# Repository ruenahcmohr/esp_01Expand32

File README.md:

# esp_01Expand32
esp-01 (esp8266) IO expander, 16 output, 16 input = 32

internet inspired esp-01 (esp8266) IO expander.

This uses DIP (socket and replace if you oops) 74xx595 and 74xx165 chips to give you 16 inputs and 16 outputs from an esp-01

Why not just use i2c?

 WELL, the i2c chips have realy primitive IO circuits, and you cannot have a high impedence input. This means you can't tie into analog circuits like RC pairs to give you time delays, which is something important to me.

 You also can't properly drive an output high, this is also important to me.

The zip file is all the gerber files to have it made.

The regultor is an AMS1117-3.3

oh yea, the power and IO are 5V., IF YOU WANT, you can bypass the regulator and use it all with 3.3V.

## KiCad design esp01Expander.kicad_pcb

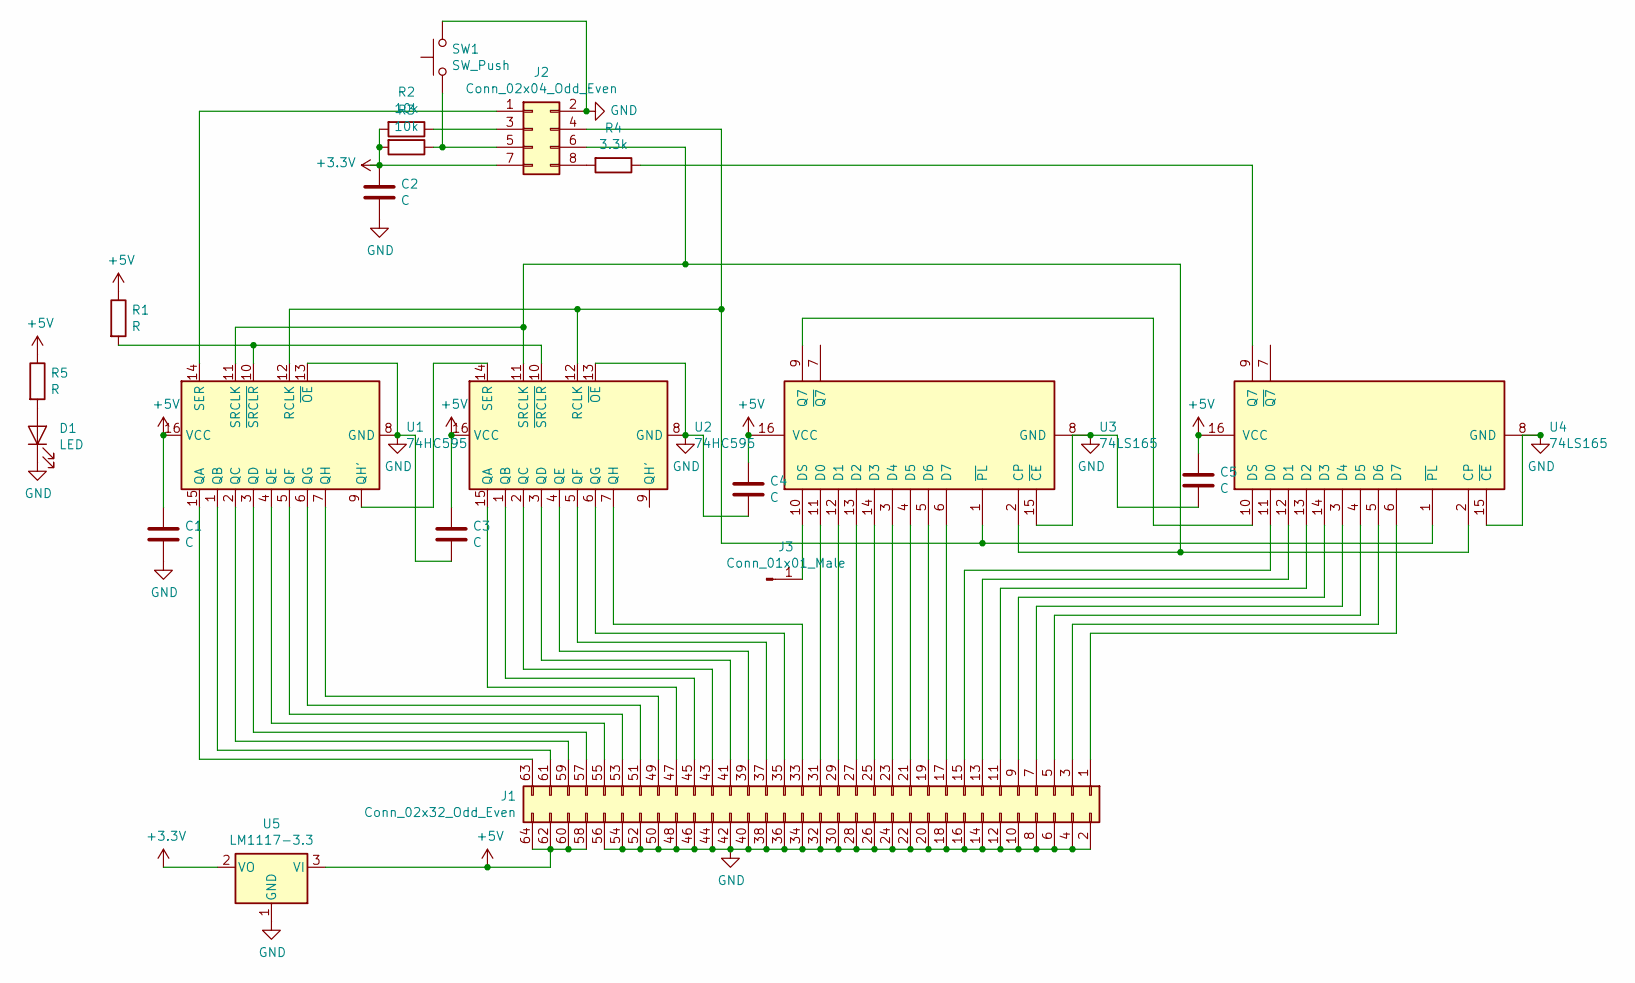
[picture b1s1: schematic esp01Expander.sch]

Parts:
C1, C2, C3, C4, C5: C; C_0805_2012Metric_Pad1.15x1.40mm_HandSolder
D1: LED; LED_0805_2012Metric_Pad1.15x1.40mm_HandSolder
J1: Conn_02x32_Odd_Even; PinHeader_2x32_P2.54mm_Vertical
J2: Conn_02x04_Odd_Even; PinHeader_2x04_P2.54mm_Vertical
J3: Conn_01x01_Male; PinHeader_1x01_P2.54mm_Vertical
R1, R5: R; R_0805_2012Metric_Pad1.15x1.40mm_HandSolder
R2, R3: 10k; R_0805_2012Metric_Pad1.15x1.40mm_HandSolder
R4: 3.3k; R_0805_2012Metric_Pad1.15x1.40mm_HandSolder
SW1: SW_Push; SW_SPST_CK_RS282G05A3
U1, U2: 74HC595; DIP-16_W7.62mm_LongPads
U3, U4: 74LS165; DIP-16_W7.62mm_LongPads
U5: LM1117-3.3; SOT-223-3_TabPin2

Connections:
+3V3: C2.1, J2.7, R2.2, R3.2, U5.2 (VO)
+5V: C1.1, C3.1, C4.1, C5.1, J1.58, J1.60, J1.62, J1.64, R1.1, R5.1, U1.16 (VCC), U2.16 (VCC), U3.16 (VCC), U4.16 (VCC), U5.3 (VI)
GND: C1.2, C2.2, C3.2, C4.2, C5.2, D1.1 (K), J1.2, J1.4, J1.6, J1.8, J1.10, J1.12, J1.14, J1.16, J1.18, J1.20, J1.22, J1.24, J1.26, J1.28, J1.30, J1.32, J1.34, J1.36, J1.38, J1.40, J1.42, J1.44, J1.46, J1.48, J1.50, J1.52, J1.54, J1.56, J2.2, SW1.2, U1.8 (GND), U1.13 (~OE), U2.8 (GND), U2.13 (~OE), U3.8 (GND), U3.15 (~CE), U4.8 (GND), U4.15 (~CE), U5.1 (GND)
unnamed: D1.2 (A), R5.2
unnamed: J1.1, U4.6 (D7)
unnamed: J1.3, U4.5 (D6)
unnamed: J1.5, U4.4 (D5)
unnamed: J1.7, U4.3 (D4)
unnamed: J1.9, U4.14 (D3)
unnamed: J1.11, U4.13 (D2)
unnamed: J1.13, U4.12 (D1)
unnamed: J1.15, U4.11 (D0)
unnamed: J1.17, U3.6 (D7)
unnamed: J1.19, U3.5 (D6)
unnamed: J1.21, U3.4 (D5)
unnamed: J1.23, U3.3 (D4)
unnamed: J1.25, U3.14 (D3)
unnamed: J1.27, U3.13 (D2)
unnamed: J1.29, U3.12 (D1)
unnamed: J1.31, U3.11 (D0)
unnamed: J1.33, U2.7 (QH)
unnamed: J1.35, U2.6 (QG)
unnamed: J1.37, U2.5 (QF)
unnamed: J1.39, U2.4 (QE)
unnamed: J1.41, U2.3 (QD)
unnamed: J1.43, U2.2 (QC)
unnamed: J1.45, U2.1 (QB)
unnamed: J1.47, U2.15 (QA)
unnamed: J1.49, U1.7 (QH)
unnamed: J1.51, U1.6 (QG)
unnamed: J1.53, U1.5 (QF)
unnamed: J1.55, U1.4 (QE)
unnamed: J1.57, U1.3 (QD)
unnamed: J1.59, U1.2 (QC)
unnamed: J1.61, U1.1 (QB)
unnamed: J1.63, U1.15 (QA)
unnamed: J2.1, U1.14 (SER)
unnamed: J2.3, R2.1
unnamed: J2.4, U1.12 (RCLK), U2.12 (RCLK), U3.1 (~PL), U4.1 (~PL)
unnamed: J2.5, R3.1, SW1.1
unnamed: J2.6, U1.11 (SRCLK), U2.11 (SRCLK), U3.2 (CP), U4.2 (CP)
unnamed: J2.8, R4.2
unnamed: J3.1, U3.10 (DS)
unnamed: R1.2, U1.10 (~SRCLR), U2.10 (~SRCLR)
unnamed: R4.1, U4.9 (Q7)
unnamed: U1.9 (QH'), U2.14 (SER)
unnamed: U3.9 (Q7), U4.10 (DS)

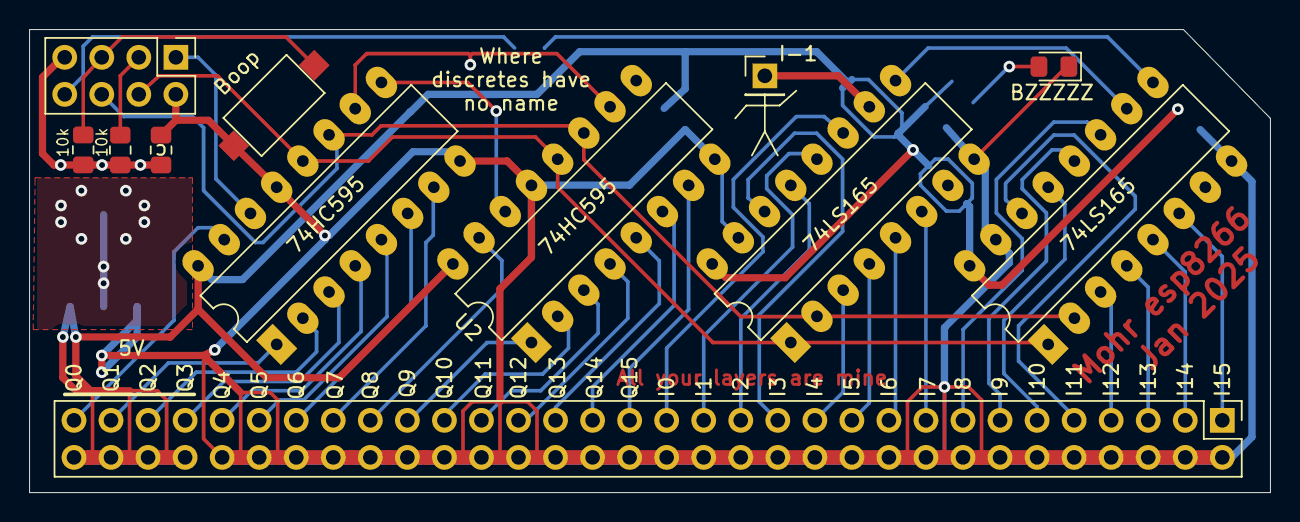
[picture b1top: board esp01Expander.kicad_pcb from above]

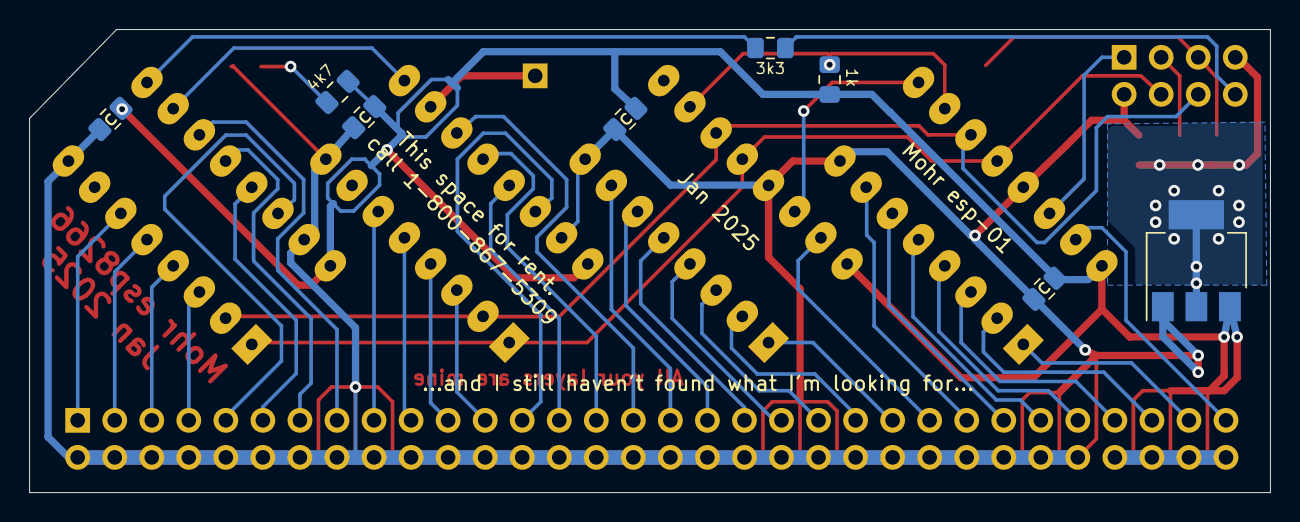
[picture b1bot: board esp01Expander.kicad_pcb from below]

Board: 2 copper layers, 85.1 x 31.8 mm, 20 parts (8 on the bottom side), 47 nets.

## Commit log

2025-02-20 adding files
2025-02-20 more images, I do actually make this stuff.
2025-02-20 oh yea, and here is some arduino source code
2025-02-20 typos!
2025-02-20 oh yea and (1)
